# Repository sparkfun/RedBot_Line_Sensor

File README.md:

RedBot Line Sensor
==================

Line following sensor for the RedBot

[  
*RedBot Line Sensor*](https://www.sparkfun.com/products/11769)

Design files and firmware files for the [RedBot Line Sensor](https://www.sparkfun.com/products/11769).

Repository Contents
-------------------

* **/Hardware** - Eagle PCB layout files
* **/Production Files** - Files to support SparkFun production

License Information
-------------------
The hardware is released under [Creative Commons ShareAlike 4.0 International](https://creativecommons.org/licenses/by-sa/4.0/).
The code is beerware; if you see me (or any other SparkFun employee) at the local, and you've found our code helpful, please buy us a round!

Distributed as-is; no warranty is given.

Authors: Mike Hord @ SparkFun Electonics

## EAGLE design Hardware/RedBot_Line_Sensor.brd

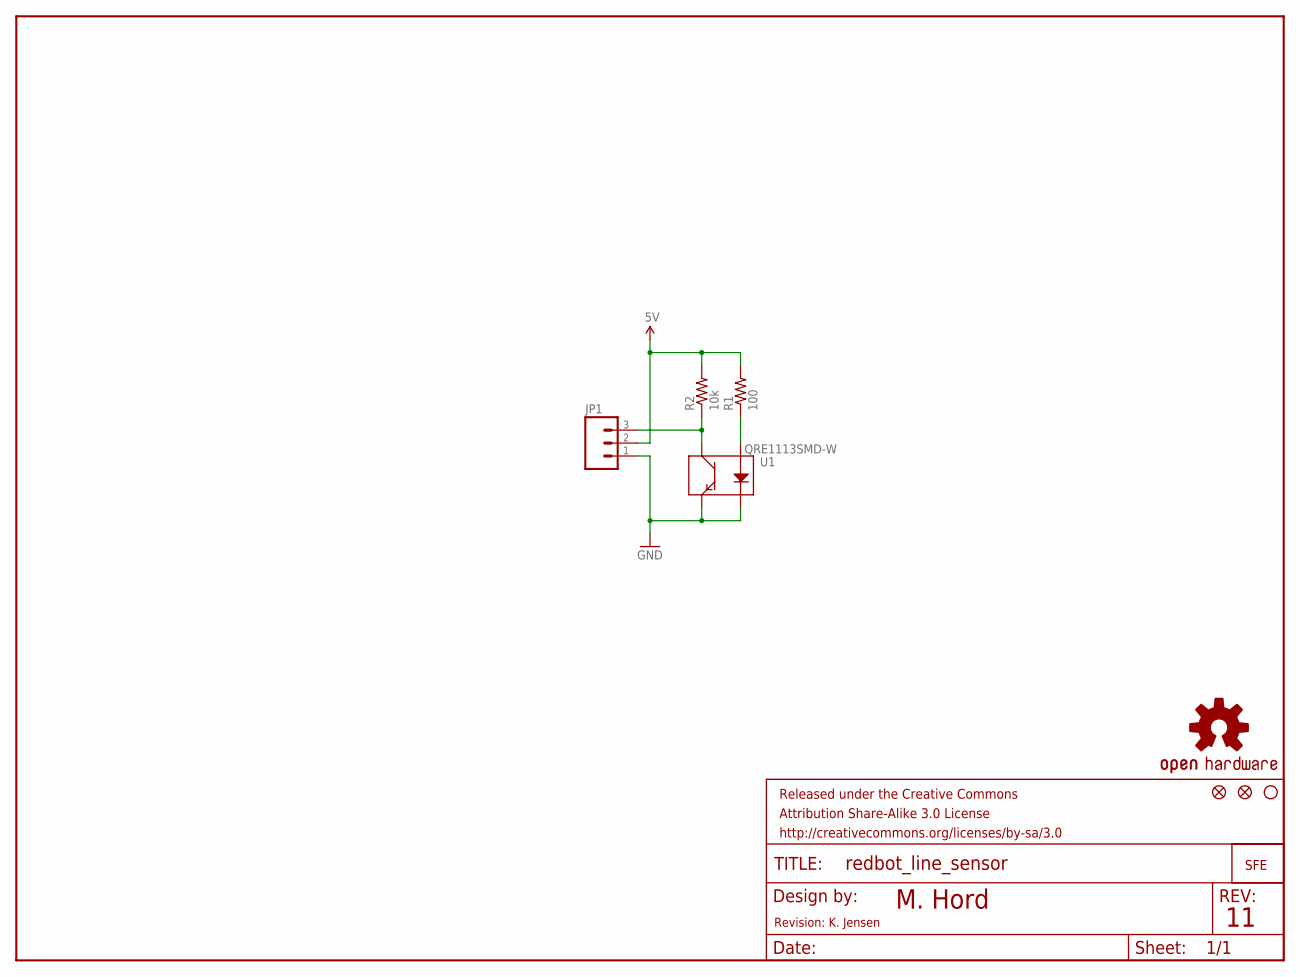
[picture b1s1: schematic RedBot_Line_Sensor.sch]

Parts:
FID1, FID2: FIDUCIAL1X2; FIDUCIAL-1X2
FRAME1: FRAME-LETTER; CREATIVE_COMMONS
JP1: M031X03_SMD_RA_MALE_POST_SMALLER; 1X03_SMD_RA_MALE_POST_SMALLER
LOGO2: OSHW-LOGOS; OSHW-LOGO-S
LOGO3: LOGO-SFESK; SFE-LOGO-FLAME
R1: 100; 0603-RES
R2: 10k; 0603-RES
STANDOFF1: STAND-OFF
U1: QRE1113SMD-W; QRE1113-W

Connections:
5V: JP1.2, R1.2, R2.2
GND: JP1.1, U1.2 (K), U1.4 (E)
unnamed: R1.1, U1.1 (A)
unnamed: JP1.3, R2.1, U1.3 (C)

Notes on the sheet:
M. Hord
Revision: K. Jensen

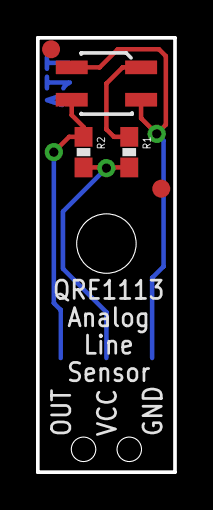
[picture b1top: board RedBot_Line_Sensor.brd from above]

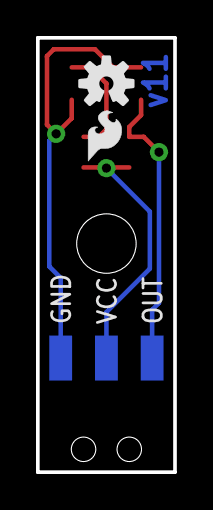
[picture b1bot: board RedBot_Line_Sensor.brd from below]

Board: 2 copper layers, 7.6 x 24.1 mm, 10 parts (3 on the bottom side), 4 nets.

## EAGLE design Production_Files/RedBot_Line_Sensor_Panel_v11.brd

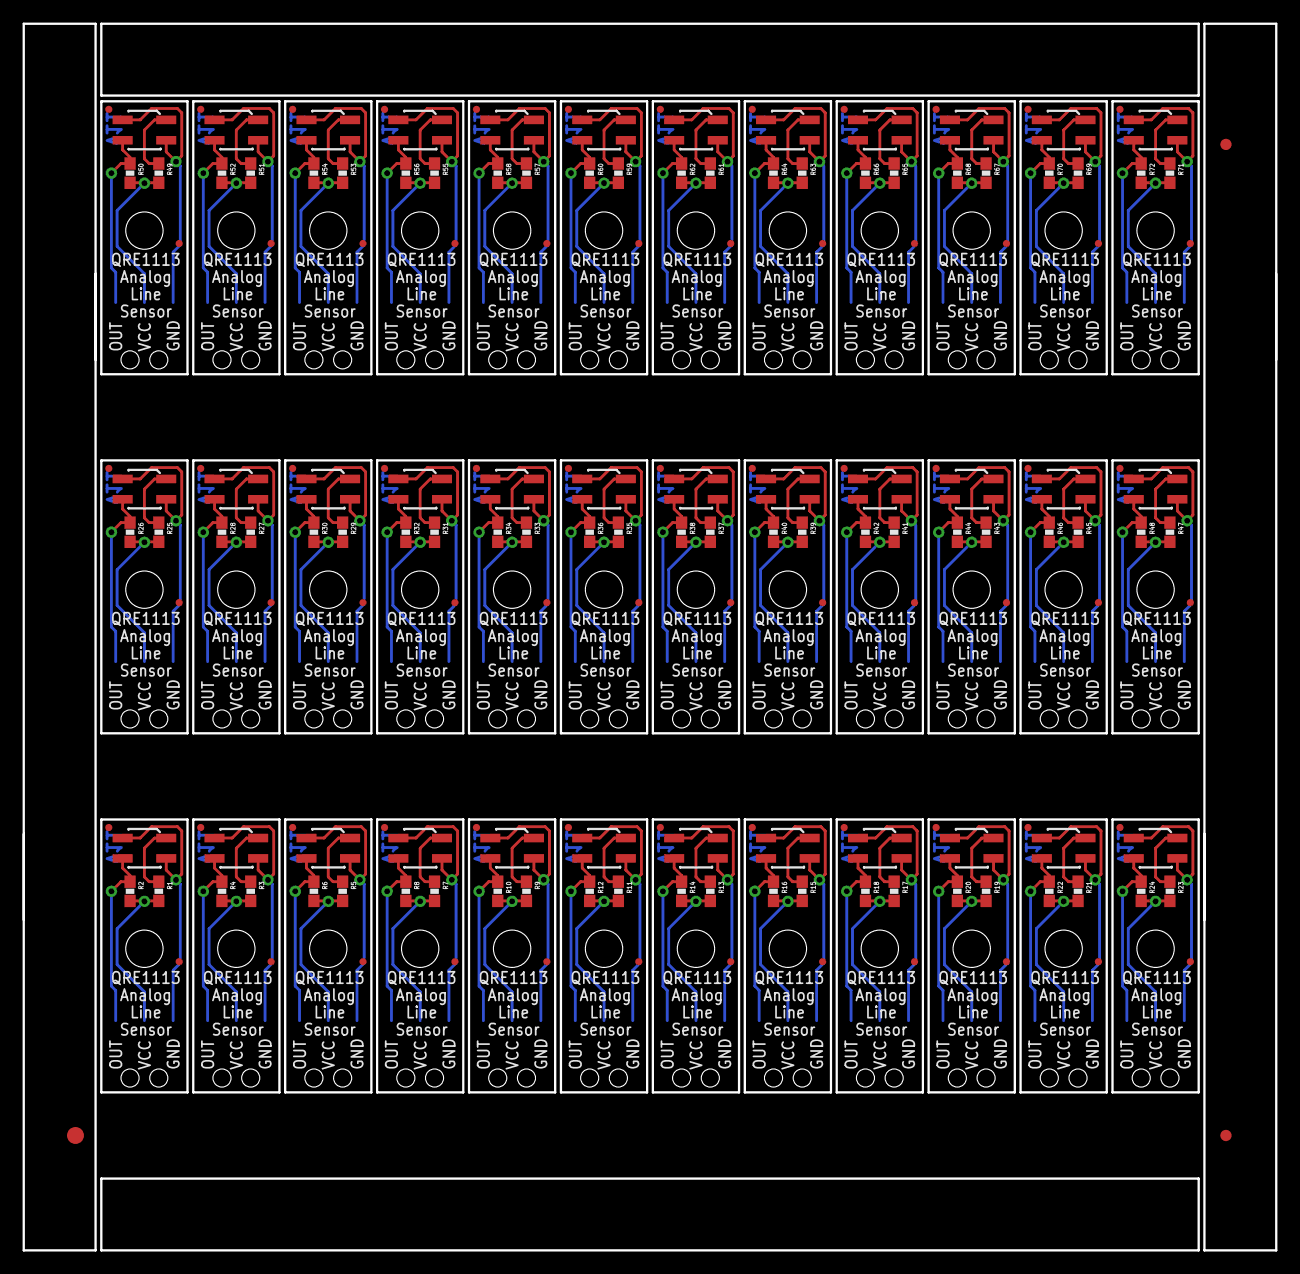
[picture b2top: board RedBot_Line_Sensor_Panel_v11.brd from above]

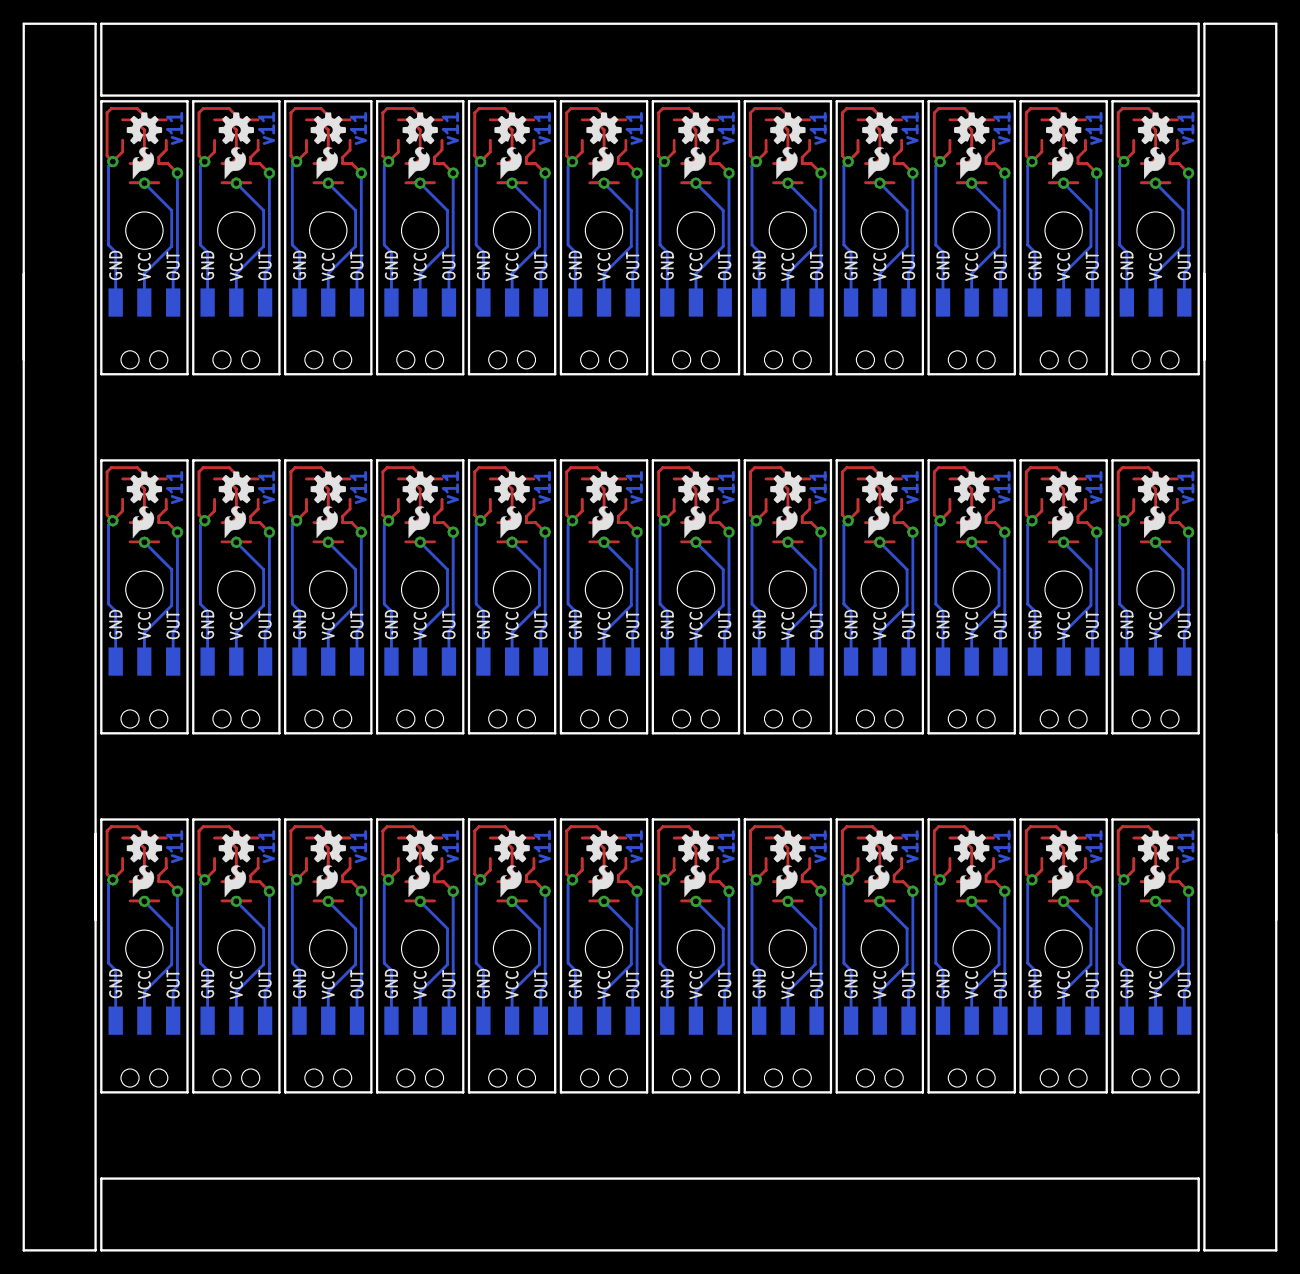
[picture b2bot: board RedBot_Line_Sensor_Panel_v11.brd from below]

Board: 2 copper layers, 110.7 x 108.5 mm, 327 parts (108 on the bottom side), 144 nets.

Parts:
E$1: FIDUCIAL-1.5X3
E$2, E$6: FIDUCIAL-1X2
FID1, FID2, FID3, FID4, FID5, FID6, FID7, FID8, FID9, FID10, FID11, FID12, FID13, FID14, FID15, FID16, FID17, FID18, FID19, FID20, FID21, FID22, FID23, FID24, FID25, FID26, FID27, FID28, FID29, FID30, FID31, FID32, FID33, FID34, FID35, FID36, FID37, FID38, FID39, FID40, FID41, FID42, FID43, FID44, FID45, FID46, FID47, FID48, FID49, FID50, FID51, FID52, FID53, FID54, FID55, FID56, FID57, FID58, FID59, FID60, FID61, FID62, FID63, FID64, FID65, FID66, FID67, FID68, FID69, FID70, FID71, FID72: FIDUCIALUFIDUCIAL; MICRO-FIDUCIAL
JP1, JP2, JP3, JP4, JP5, JP6, JP7, JP8, JP9, JP10, JP11, JP12, JP13, JP14, JP15, JP16, JP17, JP18, JP19, JP20, JP21, JP22, JP23, JP24, JP25, JP26, JP27, JP28, JP29, JP30, JP31, JP32, JP33, JP34, JP35, JP36: 1X03_SMD_RA_MALE_POST
LOGO1, LOGO2, LOGO5, LOGO7, LOGO9, LOGO11, LOGO13, LOGO15, LOGO17, LOGO19, LOGO21, LOGO23, LOGO25, LOGO27, LOGO29, LOGO31, LOGO33, LOGO35, LOGO37, LOGO39, LOGO41, LOGO43, LOGO45, LOGO47, LOGO49, LOGO51, LOGO53, LOGO55, LOGO57, LOGO59, LOGO61, LOGO63, LOGO65, LOGO67, LOGO69, LOGO71: OSHW-LOGOS; OSHW-LOGO-S
LOGO3, LOGO4, LOGO6, LOGO8, LOGO10, LOGO12, LOGO14, LOGO16, LOGO18, LOGO20, LOGO22, LOGO24, LOGO26, LOGO28, LOGO30, LOGO32, LOGO34, LOGO36, LOGO38, LOGO40, LOGO42, LOGO44, LOGO46, LOGO48, LOGO50, LOGO52, LOGO54, LOGO56, LOGO58, LOGO60, LOGO62, LOGO64, LOGO66, LOGO68, LOGO70, LOGO72: LOGO-SFESK; SFE-LOGO-FLAME
R1, R3, R5, R7, R9, R11, R13, R15, R17, R19, R21, R23, R25, R27, R29, R31, R33, R35, R37, R39, R41, R43, R45, R47, R49, R51, R53, R55, R57, R59, R61, R63, R65, R67, R69, R71: 100; 0603-RES
R2, R4, R6, R8, R10, R12, R14, R16, R18, R20, R22, R24, R26, R28, R30, R32, R34, R36, R38, R40, R42, R44, R46, R48, R50, R52, R54, R56, R58, R60, R62, R64, R66, R68, R70, R72: 10k; 0603-RES
STANDOFF1, STANDOFF2, STANDOFF3, STANDOFF4, STANDOFF5, STANDOFF6, STANDOFF7, STANDOFF8, STANDOFF9, STANDOFF10, STANDOFF11, STANDOFF12, STANDOFF13, STANDOFF14, STANDOFF15, STANDOFF16, STANDOFF17, STANDOFF18, STANDOFF19, STANDOFF20, STANDOFF21, STANDOFF22, STANDOFF23, STANDOFF24, STANDOFF25, STANDOFF26, STANDOFF27, STANDOFF28, STANDOFF29, STANDOFF30, STANDOFF31, STANDOFF32, STANDOFF33, STANDOFF34, STANDOFF35, STANDOFF36: STAND-OFF
U1, U2, U3, U4, U5, U6, U7, U8, U9, U10, U11, U12, U13, U14, U15, U16, U17, U18, U19, U20, U21, U22, U23, U24, U25, U26, U27, U28, U29, U30, U31, U32, U33, U34, U35, U36: QRE1113SMD-W; QRE1113-W

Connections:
5V: JP1.2, R1.2, R2.2
5V1: JP2.2, R3.2, R4.2
5V2: JP3.2, R5.2, R6.2
5V3: JP4.2, R7.2, R8.2
5V4: JP5.2, R9.2, R10.2
5V5: JP6.2, R11.2, R12.2
5V6: JP7.2, R13.2, R14.2
5V7: JP8.2, R15.2, R16.2
5V8: JP9.2, R17.2, R18.2
5V9: JP10.2, R19.2, R20.2
5V10: JP11.2, R21.2, R22.2
5V11: JP12.2, R23.2, R24.2
5V12: JP13.2, R25.2, R26.2
5V13: JP14.2, R27.2, R28.2
5V14: JP15.2, R29.2, R30.2
5V15: JP16.2, R31.2, R32.2
5V16: JP17.2, R33.2, R34.2
5V17: JP18.2, R35.2, R36.2
5V18: JP19.2, R37.2, R38.2
5V19: JP20.2, R39.2, R40.2
5V20: JP21.2, R41.2, R42.2
5V21: JP22.2, R43.2, R44.2
5V22: JP23.2, R45.2, R46.2
5V23: JP24.2, R47.2, R48.2
5V24: JP25.2, R49.2, R50.2
5V25: JP26.2, R51.2, R52.2
5V26: JP27.2, R53.2, R54.2
5V27: JP28.2, R55.2, R56.2
5V28: JP29.2, R57.2, R58.2
5V29: JP30.2, R59.2, R60.2
5V30: JP31.2, R61.2, R62.2
5V31: JP32.2, R63.2, R64.2
5V32: JP33.2, R65.2, R66.2
5V33: JP34.2, R67.2, R68.2
5V34: JP35.2, R69.2, R70.2
5V35: JP36.2, R71.2, R72.2
GND: JP1.1, U1.2, U1.4
GND1: JP2.1, U2.2, U2.4
GND2: JP3.1, U3.2, U3.4
GND3: JP4.1, U4.2, U4.4
GND4: JP5.1, U5.2, U5.4
GND5: JP6.1, U6.2, U6.4
GND6: JP7.1, U7.2, U7.4
GND7: JP8.1, U8.2, U8.4
GND8: JP9.1, U9.2, U9.4
GND9: JP10.1, U10.2, U10.4
GND10: JP11.1, U11.2, U11.4
GND11: JP12.1, U12.2, U12.4
GND12: JP13.1, U13.2, U13.4
GND13: JP14.1, U14.2, U14.4
GND14: JP15.1, U15.2, U15.4
GND15: JP16.1, U16.2, U16.4
GND16: JP17.1, U17.2, U17.4
GND17: JP18.1, U18.2, U18.4
GND18: JP19.1, U19.2, U19.4
GND19: JP20.1, U20.2, U20.4
GND20: JP21.1, U21.2, U21.4
GND21: JP22.1, U22.2, U22.4
GND22: JP23.1, U23.2, U23.4
GND23: JP24.1, U24.2, U24.4
GND24: JP25.1, U25.2, U25.4
GND25: JP26.1, U26.2, U26.4
GND26: JP27.1, U27.2, U27.4
GND27: JP28.1, U28.2, U28.4
GND28: JP29.1, U29.2, U29.4
GND29: JP30.1, U30.2, U30.4
GND30: JP31.1, U31.2, U31.4
GND31: JP32.1, U32.2, U32.4
GND32: JP33.1, U33.2, U33.4
GND33: JP34.1, U34.2, U34.4
GND34: JP35.1, U35.2, U35.4
GND35: JP36.1, U36.2, U36.4
unnamed: R1.1, U1.1
unnamed: JP1.3, R2.1, U1.3
unnamed: R3.1, U2.1
unnamed: JP2.3, R4.1, U2.3
unnamed: R5.1, U3.1
unnamed: JP3.3, R6.1, U3.3
unnamed: R7.1, U4.1
unnamed: JP4.3, R8.1, U4.3
unnamed: R9.1, U5.1
unnamed: JP5.3, R10.1, U5.3
unnamed: R11.1, U6.1
unnamed: JP6.3, R12.1, U6.3
unnamed: R13.1, U7.1
unnamed: JP7.3, R14.1, U7.3
unnamed: R15.1, U8.1
unnamed: JP8.3, R16.1, U8.3
unnamed: R17.1, U9.1
unnamed: JP9.3, R18.1, U9.3
unnamed: R19.1, U10.1
unnamed: JP10.3, R20.1, U10.3
unnamed: R21.1, U11.1
unnamed: JP11.3, R22.1, U11.3
unnamed: R23.1, U12.1
unnamed: JP12.3, R24.1, U12.3
unnamed: R25.1, U13.1
unnamed: JP13.3, R26.1, U13.3
unnamed: R27.1, U14.1
unnamed: JP14.3, R28.1, U14.3
unnamed: R29.1, U15.1
unnamed: JP15.3, R30.1, U15.3
unnamed: R31.1, U16.1
unnamed: JP16.3, R32.1, U16.3
unnamed: R33.1, U17.1
unnamed: JP17.3, R34.1, U17.3
unnamed: R35.1, U18.1
unnamed: JP18.3, R36.1, U18.3
unnamed: R37.1, U19.1
unnamed: JP19.3, R38.1, U19.3
unnamed: R39.1, U20.1
unnamed: JP20.3, R40.1, U20.3
unnamed: R41.1, U21.1
unnamed: JP21.3, R42.1, U21.3
unnamed: R43.1, U22.1
unnamed: JP22.3, R44.1, U22.3
unnamed: R45.1, U23.1
unnamed: JP23.3, R46.1, U23.3
unnamed: R47.1, U24.1
unnamed: JP24.3, R48.1, U24.3
unnamed: R49.1, U25.1
unnamed: JP25.3, R50.1, U25.3
unnamed: R51.1, U26.1
unnamed: JP26.3, R52.1, U26.3
unnamed: R53.1, U27.1
unnamed: JP27.3, R54.1, U27.3
unnamed: R55.1, U28.1
unnamed: JP28.3, R56.1, U28.3
unnamed: R57.1, U29.1
unnamed: JP29.3, R58.1, U29.3
unnamed: R59.1, U30.1
unnamed: JP30.3, R60.1, U30.3
unnamed: R61.1, U31.1
unnamed: JP31.3, R62.1, U31.3
unnamed: R63.1, U32.1
unnamed: JP32.3, R64.1, U32.3
unnamed: R65.1, U33.1
unnamed: JP33.3, R66.1, U33.3
unnamed: R67.1, U34.1
unnamed: JP34.3, R68.1, U34.3
unnamed: R69.1, U35.1
unnamed: JP35.3, R70.1, U35.3
unnamed: R71.1, U36.1
unnamed: JP36.3, R72.1, U36.3

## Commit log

2013-03-08 v01 files for protos
2013-05-15 Change to Rev 10 for release - flipped connector to bottom side of board - change revision number
2013-05-15 Move board name silk to top
2013-05-17 Production Readied
    Added fiducial reference points & created panel for manufacture.
2013-06-12 Added text to panel file to indicate mill areas
2013-12-04 QC Revision
    Changes:
    1.) 0402 to 0603 footprint
    2.) Updated QRE1113 footprint
    3.) New 3-pin SMD header footprint w/ bosses
2013-12-10 Minor aesthetic fixes
    1.) Moved VCC via away from silk
    2.) Moved board name silk away from header boss holes
    3.) Updated version info in schematic.
    4.) Moved flame on top side out to avoid resistor tcreme.
2014-01-30 Silk fixes and trace reroutes
    Fixed top silk so pin labels are closer to edge of board and nothing
    gets cut off. Removed flame from top. Cleaned up "out" and "vcc" traces
    to be more efficient.
2014-01-30 Created Panel v11
2014-05-20 Updating README
2014-07-30 Updating 3 pin connector package
    Updating 3 pin connector package to use new footprint that drops drill
    hits for the connector's bosses down from 0.062' to 0.0535'. This will
    help keep the part straight during reflow.
2014-08-06 removed micro fid. added regular
2014-08-06 created panel v11a
    This panel will have proper spacing for the plastic cap on the 3 pin
    header.
2015-03-25 corrected folder name
2025-06-27 Update README.md
    Updating link

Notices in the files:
parts and their libraries:
SparkFun-Aesthetics: Licensing: CC v3.0 Share-Alike You are welcome to use this library for commercial purposes.
SparkFun-Aesthetics: Released under the Creative Commons Attribution Share-Alike 3.0 License
SparkFun-Aesthetics: http://creativecommons.org/licenses/by-sa/3.0
